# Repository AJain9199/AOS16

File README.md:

<!-- Improved compatibility of back to top link: See: https://github.com/othneildrew/Best-README-Template/pull/73 -->

<!--
*** Thanks for checking out the Best-README-Template. If you have a suggestion
*** that would make this better, please fork the repo and create a pull request
*** or simply open an issue with the tag "enhancement".
*** Don't forget to give the project a star!
*** Thanks again! Now go create something AMAZING! :D
-->

<!-- PROJECT SHIELDS -->
<!--
*** I'm using markdown "reference style" links for readability.
*** Reference links are enclosed in brackets [ ] instead of parentheses ( ).
*** See the bottom of this document for the declaration of the reference variables
*** for contributors-url, forks-url, etc. This is an optional, concise syntax you may use.
*** https://www.markdownguide.org/basic-syntax/#reference-style-links
-->

<!-- PROJECT LOGO -->
<br />
<div align="center">
    
    <h1 align="center">AOS16</h1>
  <p align="center">
    A self-made 16-bit computer.
  </p>
</div>

<!-- TABLE OF CONTENTS -->
<details>
  <summary>Table of Contents</summary>
  <ol>
    <li>
      <a href="#about-the-project">About The Project</a>
    </li>
    <li><a href="#pictures">Pictures</a></li>
    <li><a href="#technical-details">Technical Details</a></li>
    <li><a href="#directory-structure">Directory Structure</a></li>
    <li><a href="#to-do">To-Do</a></li>
    <li><a href="#acknowledgments">Acknowledgments</a></li>
  </ol>
</details>

<!-- ABOUT THE PROJECT -->

## About The Project

AOS16 is a self-made 16-bit Reduced Instruction Set Computer (RISC) on PCBs, complete with a homebrew GPU for screen output. It is fully planned, designed and fabricated from scratch. A Turing-complete, Harvard-style computer with a completely custom architecture, at a blistering fast 10MHz.

The project is divided into smaller subsytems on PCBs, designed to interconnect via a central bus.

### Features
- 16-bit address and data buses
- Hardware double buffering with parallel CPU and GPU operation
- 10 MHz clock
- 6 general-purpose registers, a stack pointer and a flags register
- 65 Kb of general purpose RAM
- 131 Kb of framebuffer (double buffered, so 65Kb usable)
- 131 Kb of program memory

### Why?

This project was a learning effort for me. I started this project wanting to learn more about computer architectures and gain hands-on experience with electrical engineering. Also, building a computer, from scratch, is the coolest project I've seen around. Some inspiration from amazing engineers including Ben Eater and jdh were more than enough to convince me to try my hand at this project.

### How's it different?

Most homebrew computers on the internet are 8-bit computers built on breadboards.  AOS16 is novel in its capabilities, being a 16-bit computer built on PCBs with a much higher clock speed, with display support directly integrated. 

<p align="right">(<a href="#readme-top">back to top</a>)</p>

## Pictures

<!-- The animated GIFs will not be visible in the PDF! Please visit the repository on [Github](https://github.com/AJain9199/AOS16). -->

<h2 align="center">
A simulation of the computer in Digital displaying the color palette on the screen
</h2>

<br>

<h2 align="center">
    GPU displaying the pillars of creation
</h2>

<br>

<h2 align="center">
    The Arithmetic Logic Unit in KiCAD
</h2>

<br>

<h2 align="center">
    The logic simulation in Digital.
</h2>

<br>

<h2 align="center">
    The Reg4x16 PCB 
</h2>

<br>

.jpeg>)

<h2 align="center">
    The Double Buffer PCB
</h2>

<br>

<p align="right">(<a href="#readme-top">back to top</a>)</p>

## Technical Details

Details about the design decisions, design of the instruction word, etc. can be found in the [Design Doc](AOS-16%20Design.md).

## Directory Structure

- assembler: Contains the source code for the AOS16 assembler
- sim: Logic simulation files written for Digital
- microcode: Microcode implementations written in MiLa
- tests: some basic tests for ICs and the simulation
- common: basic KiCAD schematics (registers, transceivers) which are shared across subsystems

Each of the remaining folders represents a subsystem, built on a separate PCB. Each folder will contain a KiCAD schematic and PCB file.

## To-do

Main Phases of the project:

-   [x] Finalize project parameters and design goals
-   [ ] Hardware:
    -   [x] Logic Simulation and Design
    -   [ ] PCB Design
    -   [ ] PCB Fabrication & integration
-   [x] Software:
    -   [x] Microcode (with [MiLa](https://github.com/AJain9199/MiLa))
    -   [x] Assembly language design
    -   [x] Assembler
    -   [x] ROM programming software

<br>

| Component / Phase   | Logic Simulation | PCB Design | Fabrication and Integration |
| ------------------- | ---------------- | ---------- | --------------------------- |
| Double Buffer       | ✅               | ✅         | ✅                 |
| Memory Controller   | ✅               | ✅         | ✅                 |
| ALU                 | ✅               | ✅         | ✅                          |
| Registers           | ✅               | ✅         | ✅                          |
| Control Unit        | ✅               | ✅          |  ✅                          |
| Program Counter     | ✅               | ✅         |  ☐                           |
| GPU                 | ✅               | ✅          | ☐                           |
| Main Data Bus       | ✅               | ✅          | ☐                           |
| **Phase Completed** | ✅               | ✅          | ☐                           |

<p align="right">(<a href="#readme-top">back to top</a>)</p>

<!-- ACKNOWLEDGMENTS -->
## Acknowledgments

-   [Ben Eater](https://www.youtube.com/@BenEater) for his excellent series on the breadboard computer
-   [jdh](https://www.youtube.com/@jdh) for the inspiration
-   The Elements of Computing Systems and the accompanying [Nand2Tetris](https://www.nand2tetris.org/) course by Shimon Schocken and Noam Nisan
-   [r/homebrewcomputer](https://www.reddit.com/r/homebrewcomputer/) and [r/PrintedCircuitBoard](https://www.reddit.com/r/PrintedCircuitBoard/) commmunities for PCB reviews and design checks
-   [Digital](https://github.com/hneemann/Digital), the logic simulator

<p align="right">(<a href="#readme-top">back to top</a>)</p>

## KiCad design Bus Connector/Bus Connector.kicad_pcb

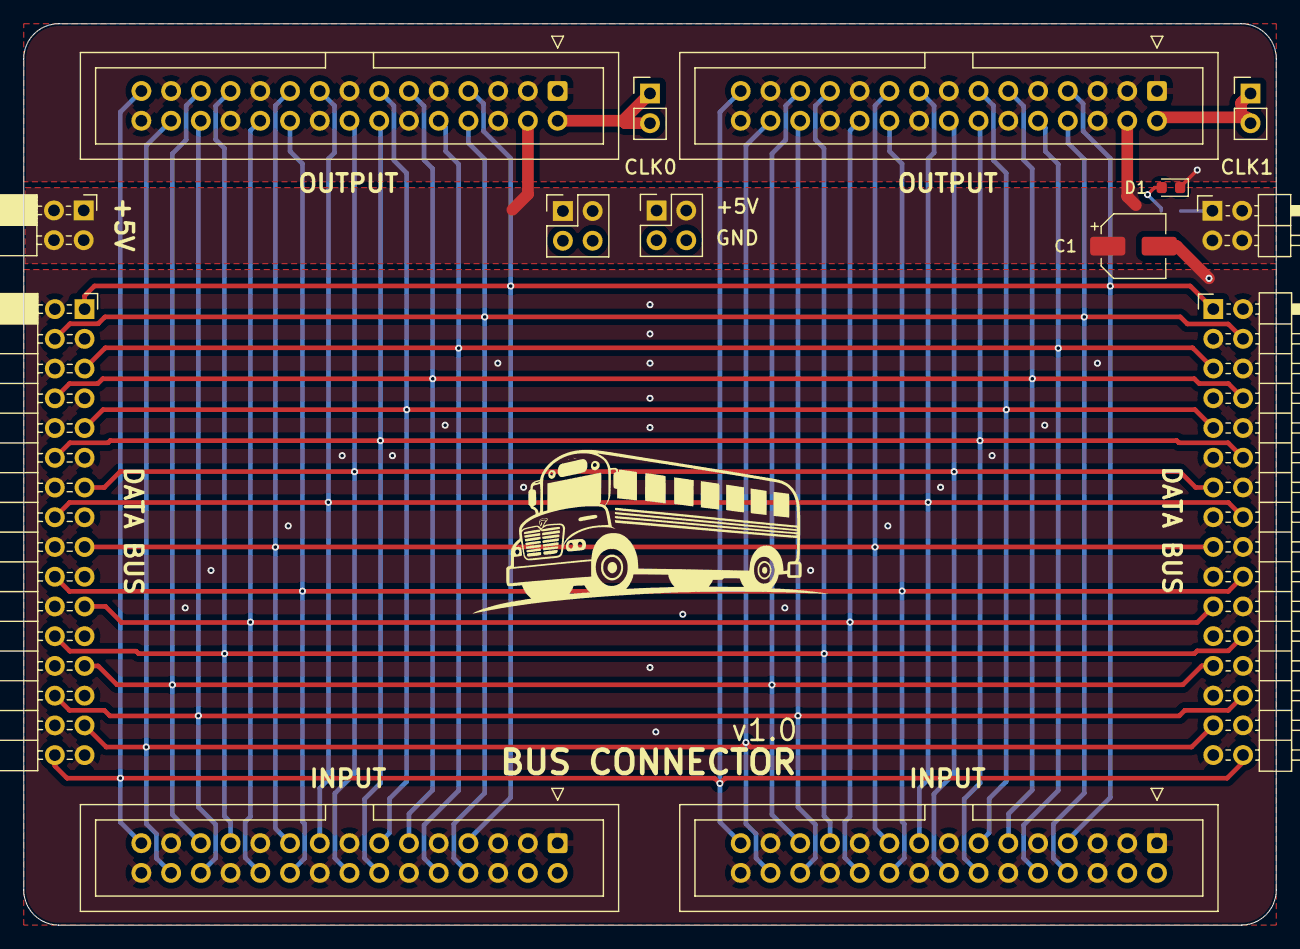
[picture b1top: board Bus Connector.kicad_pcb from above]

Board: 2 copper layers, 107.0 x 77.0 mm, 15 parts (1 on the bottom side), 21 nets.

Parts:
C1: 100uF; CP_Elec_5x5.3
D1: LED; LED_0603_1608Metric
J1: Conn_02x16_Odd_Even; PinSocket_2x16_P2.54mm_Horizontal
J2: Conn_02x16_Odd_Even; PinHeader_2x16_P2.54mm_Horizontal
J3: Conn_02x02_Counter_Clockwise; PinHeader_2x02_P2.54mm_Horizontal
J4: Conn_02x02_Counter_Clockwise; PinSocket_2x02_P2.54mm_Horizontal
J5, J6, J7, J8: Conn_02x15_Odd_Even; IDC-Header_2x15_P2.54mm_Vertical
J9, J10: Conn_01x02_Pin; PinHeader_1x02_P2.54mm_Vertical
J11, J12: Conn_02x02_Counter_Clockwise; PinHeader_2x02_P2.54mm_Vertical
R1: 220; R_0603_1608Metric

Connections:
+5V: C1.1, J3.1, J3.2, J3.3, J3.4, J4.1, J4.2, J4.3, J4.4, J7.4, J8.4, J11.1, J11.2, J12.1, J12.2, R1.1
/IO0: J1.1, J2.1, J5.7, J6.7, J7.7, J8.7
/IO1: J1.4, J2.4, J5.8, J6.8, J7.8, J8.8
/IO2: J1.5, J2.5, J5.10, J6.10, J7.10, J8.10
/IO3: J1.8, J2.8, J5.11, J6.11, J7.11, J8.11
/IO4: J1.9, J2.9, J5.13, J6.13, J7.13, J8.13
/IO5: J1.12, J2.12, J5.14, J6.14, J7.14, J8.14
/IO6: J1.13, J2.13, J5.16, J6.16, J7.16, J8.16
/IO7: J1.16, J2.16, J5.17, J6.17, J7.17, J8.17
/IO8: J1.17, J2.17, J5.19, J6.19, J7.19, J8.19
/IO9: J1.20, J2.20, J5.20, J6.20, J7.20, J8.20
/IO10: J1.21, J2.21, J5.22, J6.22, J7.22, J8.22
/IO11: J1.24, J2.24, J5.23, J6.23, J7.23, J8.23
/IO12: J1.25, J2.25, J5.25, J6.25, J7.25, J8.25
/IO13: J1.28, J2.28, J5.26, J6.26, J7.26, J8.26
/IO14: J1.29, J2.29, J5.28, J6.28, J7.28, J8.28
/IO15: J1.32, J2.32, J5.29, J6.29, J7.29, J8.29
/bus_conn2/CLK: J7.2, J10.1, J10.2
/bus_conn3/CLK: J8.2, J9.1, J9.2
GND: C1.2, D1.1 (K), J1.2, J1.3, J1.6, J1.7, J1.10, J1.11, J1.14, J1.15, J1.18, J1.19, J1.22, J1.23, J1.26, J1.27, J1.30, J1.31, J2.2, J2.3, J2.6, J2.7, J2.10, J2.11, J2.14, J2.15, J2.18, J2.19, J2.22, J2.23, J2.26, J2.27, J2.30, J2.31, J5.1, J5.3, J5.5, J5.6, J5.9, J5.12, J5.15, J5.18, J5.21, J5.24, J5.27, J5.30, J6.1, J6.3, J6.5, J6.6, J6.9, J6.12, J6.15, J6.18, J6.21, J6.24, J6.27, J6.30, J7.1, J7.3, J7.5, J7.6, J7.9, J7.12, J7.15, J7.18, J7.21, J7.24, J7.27, J7.30, J8.1, J8.3, J8.5, J8.6, J8.9, J8.12, J8.15, J8.18, J8.21, J8.24, J8.27, J8.30, J11.3, J11.4, J12.3, J12.4
unnamed: D1.2 (A), R1.2

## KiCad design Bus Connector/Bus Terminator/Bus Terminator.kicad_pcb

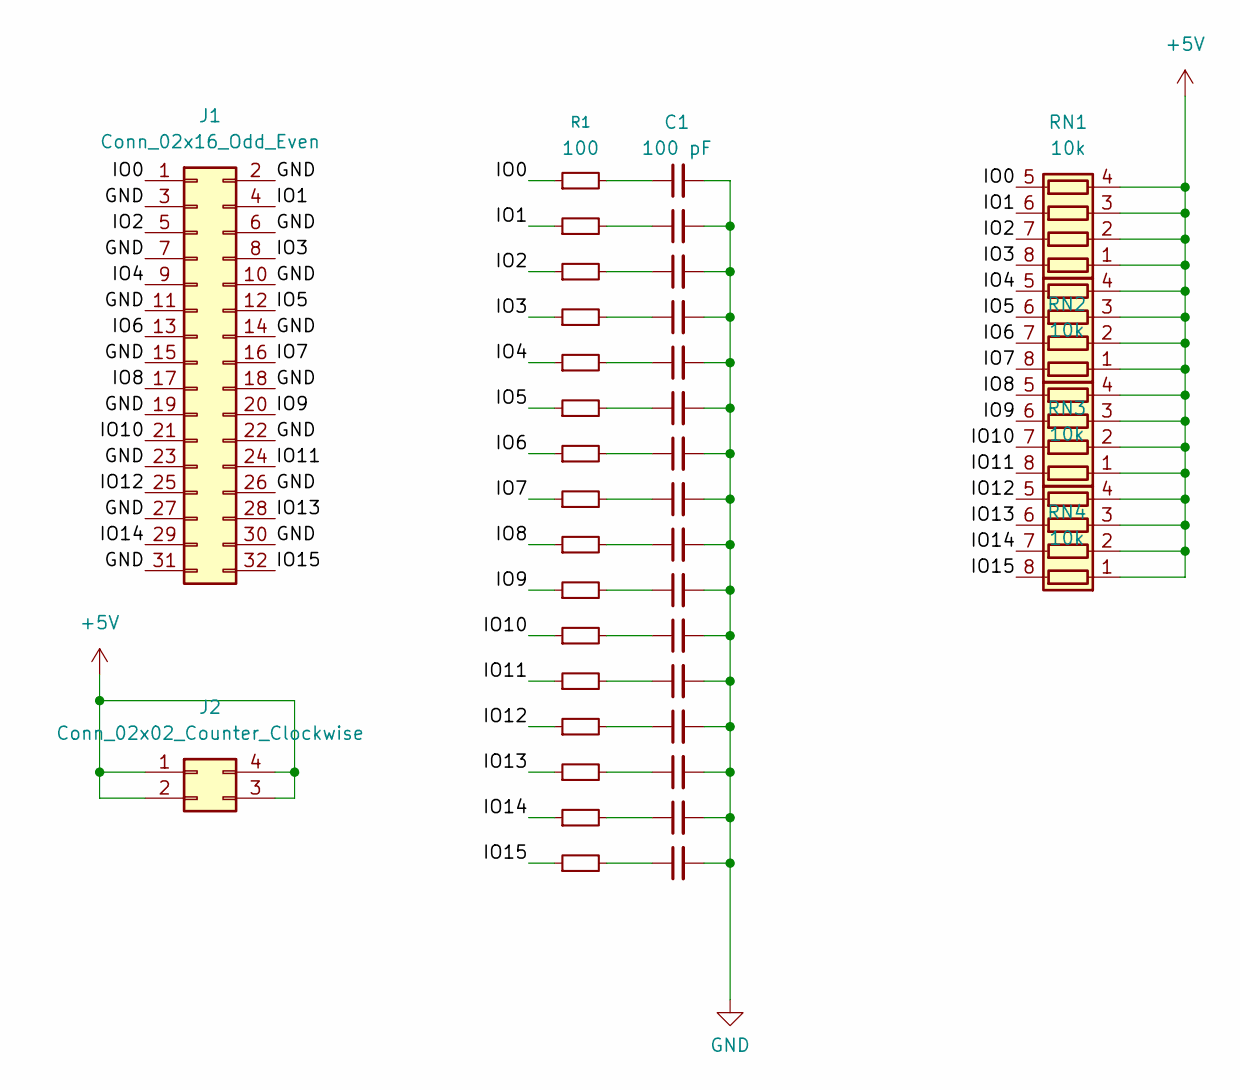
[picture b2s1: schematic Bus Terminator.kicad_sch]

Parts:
C1, C2, C3, C4, C5, C6, C7, C8, C9, C10, C11, C12, C13, C14, C15, C16: 100 pF; C_0603_1608Metric
J1: Conn_02x16_Odd_Even; PinHeader_2x16_P2.54mm_Horizontal
J2: Conn_02x02_Counter_Clockwise; PinHeader_2x02_P2.54mm_Horizontal
R1, R2, R3, R4, R5, R6, R7, R8, R9, R10, R11, R12, R13, R14, R15, R16: 100; R_0603_1608Metric
RN1, RN2, RN3, RN4: 10k; R_Array_Convex_4x1206

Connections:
+5V: J2.1, J2.2, J2.3, J2.4, RN1.1 (R1.1), RN1.2 (R2.1), RN1.3 (R3.1), RN1.4 (R4.1), RN2.1 (R1.1), RN2.2 (R2.1), RN2.3 (R3.1), RN2.4 (R4.1), RN3.1 (R1.1), RN3.2 (R2.1), RN3.3 (R3.1), RN3.4 (R4.1), RN4.1 (R1.1), RN4.2 (R2.1), RN4.3 (R3.1), RN4.4 (R4.1)
/IO0: J1.1, R1.1, RN1.5 (R4.2)
/IO1: J1.4, R2.1, RN1.6 (R3.2)
/IO2: J1.5, R3.1, RN1.7 (R2.2)
/IO3: J1.8, R4.1, RN1.8 (R1.2)
/IO4: J1.9, R5.1, RN2.5 (R4.2)
/IO5: J1.12, R6.1, RN2.6 (R3.2)
/IO6: J1.13, R7.1, RN2.7 (R2.2)
/IO7: J1.16, R8.1, RN2.8 (R1.2)
/IO8: J1.17, R9.1, RN3.5 (R4.2)
/IO9: J1.20, R10.1, RN3.6 (R3.2)
/IO10: J1.21, R11.1, RN3.7 (R2.2)
/IO11: J1.24, R12.1, RN3.8 (R1.2)
/IO12: J1.25, R13.1, RN4.5 (R4.2)
/IO13: J1.28, R14.1, RN4.6 (R3.2)
/IO14: J1.29, R15.1, RN4.7 (R2.2)
/IO15: J1.32, R16.1, RN4.8 (R1.2)
GND: C1.2, C2.2, C3.2, C4.2, C5.2, C6.2, C7.2, C8.2, C9.2, C10.2, C11.2, C12.2, C13.2, C14.2, C15.2, C16.2, J1.2, J1.3, J1.6, J1.7, J1.10, J1.11, J1.14, J1.15, J1.18, J1.19, J1.22, J1.23, J1.26, J1.27, J1.30, J1.31
unnamed: C1.1, R1.2
unnamed: C2.1, R2.2
unnamed: C3.1, R3.2
unnamed: C4.1, R4.2
unnamed: C5.1, R5.2
unnamed: C6.1, R6.2
unnamed: C7.1, R7.2
unnamed: C8.1, R8.2
unnamed: C9.1, R9.2
unnamed: C10.1, R10.2
unnamed: C11.1, R11.2
unnamed: C12.1, R12.2
unnamed: C13.1, R13.2
unnamed: C14.1, R14.2
unnamed: C15.1, R15.2
unnamed: C16.1, R16.2

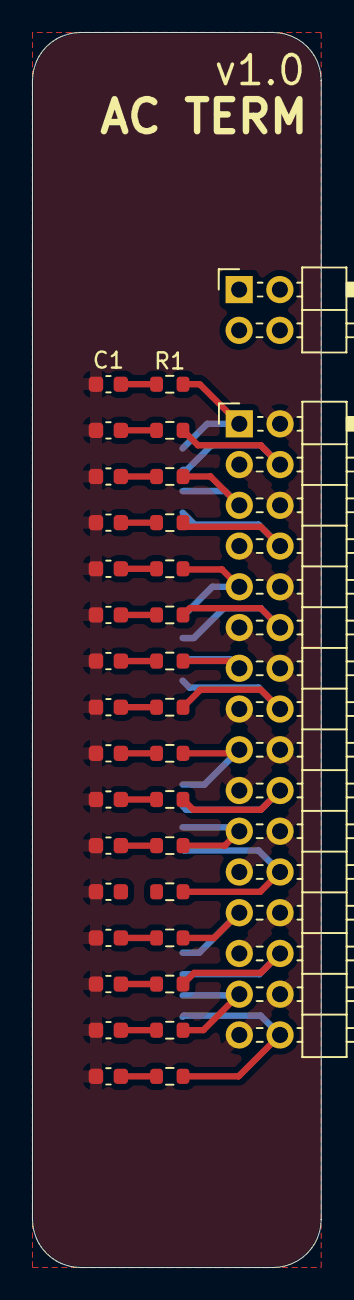
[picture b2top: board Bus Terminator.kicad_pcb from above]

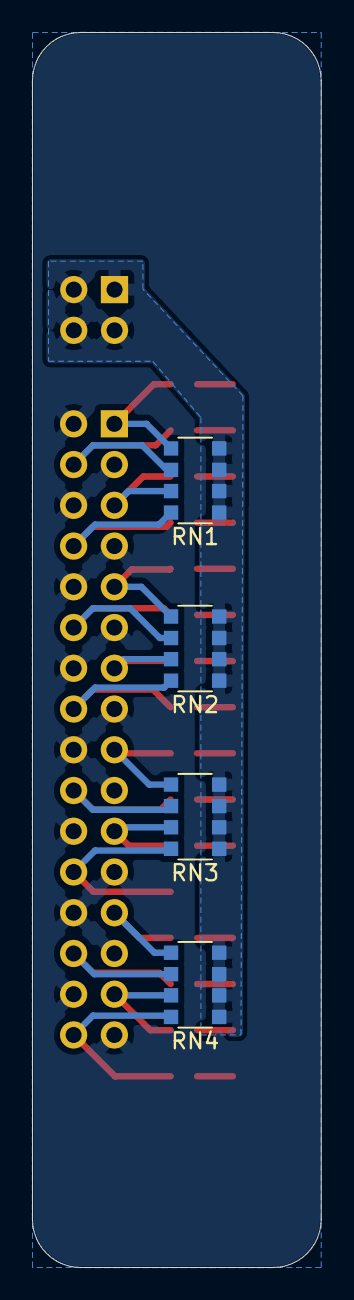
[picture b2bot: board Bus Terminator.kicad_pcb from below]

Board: 2 copper layers, 18.0 x 77.0 mm, 38 parts (4 on the bottom side), 34 nets.

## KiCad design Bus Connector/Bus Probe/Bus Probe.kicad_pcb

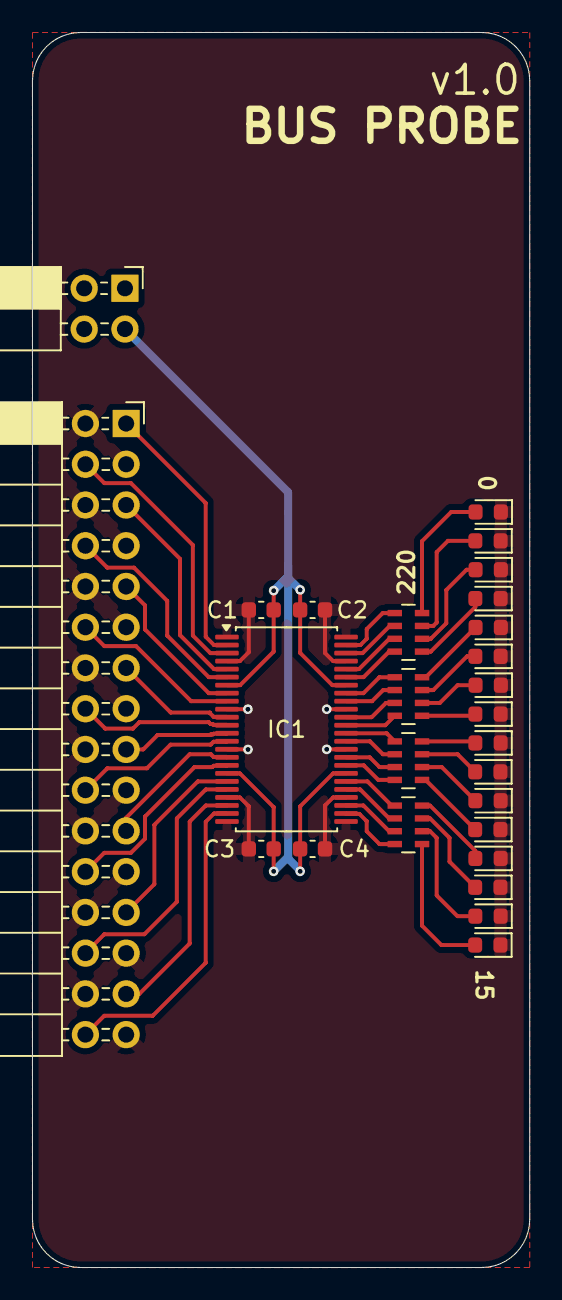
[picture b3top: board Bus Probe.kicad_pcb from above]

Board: 2 copper layers, 31.0 x 77.0 mm, 27 parts (0 on the bottom side), 50 nets.

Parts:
C1, C2, C3, C4: 0.01uF; C_0603_1608Metric
D1, D2, D3, D4, D5, D6, D7, D8, D9, D10, D11, D12, D13, D14, D15, D16: LED_Small; LED_0603_1608Metric
IC1: SN74AHCT16245DGGR; TSSOP-48_6.1x12.5mm_P0.5mm
J1: Conn_02x16_Odd_Even; PinSocket_2x16_P2.54mm_Horizontal
J2: Conn_02x02_Counter_Clockwise; PinSocket_2x02_P2.54mm_Horizontal
RN1, RN2, RN3, RN4: R_Pack04; R_Array_Concave_4x0603

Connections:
+5V: C1.1, C2.1, C3.1, C4.1, IC1.7 (VCC), IC1.18 (VCC), IC1.31 (VCC), IC1.42 (VCC), J2.1, J2.2, J2.3, J2.4
/B0: IC1.47 (A0), RN1.1 (R1.1)
/B1: IC1.46 (A1), RN1.2 (R2.1)
/B2: IC1.44 (A2), RN1.3 (R3.1)
/B3: IC1.43 (A3), RN1.4 (R4.1)
/B4: IC1.41 (A4), RN2.1 (R1.1)
/B5: IC1.40 (A5), RN2.2 (R2.1)
/B6: IC1.38 (A6), RN2.3 (R3.1)
/B7: IC1.37 (A7), RN2.4 (R4.1)
/B8: IC1.36 (A8), RN3.1 (R1.1)
/B9: IC1.35 (A9), RN3.2 (R2.1)
/B10: IC1.33 (A10), RN3.3 (R3.1)
/B11: IC1.32 (A11), RN3.4 (R4.1)
/B12: IC1.30 (A12), RN4.1 (R1.1)
/B13: IC1.29 (A13), RN4.2 (R2.1)
/B14: IC1.27 (A14), RN4.3 (R3.1)
/B15: IC1.26 (A15), RN4.4 (R4.1)
/IO0: IC1.2 (B0), J1.1
/IO1: IC1.3 (B1), J1.4
/IO2: IC1.5 (B2), J1.5
/IO3: IC1.6 (B3), J1.8
/IO4: IC1.8 (B4), J1.9
/IO5: IC1.9 (B5), J1.12
/IO6: IC1.11 (B6), J1.13
/IO7: IC1.12 (B7), J1.16
/IO8: IC1.13 (B8), J1.17
/IO9: IC1.14 (B9), J1.20
/IO10: IC1.16 (B10), J1.21
/IO11: IC1.17 (B11), J1.24
/IO12: IC1.19 (B12), J1.25
/IO13: IC1.20 (B13), J1.28
/IO14: IC1.22 (B14), J1.29
/IO15: IC1.23 (B15), J1.32
GND: C1.2, C2.2, C3.2, C4.2, D1.1 (K), D2.1 (K), D3.1 (K), D4.1 (K), D5.1 (K), D6.1 (K), D7.1 (K), D8.1 (K), D9.1 (K), D10.1 (K), D11.1 (K), D12.1 (K), D13.1 (K), D14.1 (K), D15.1 (K), D16.1 (K), IC1.1 (T/~R1), IC1.4 (GND), IC1.10 (GND), IC1.15 (GND), IC1.21 (GND), IC1.24 (T/~R2), IC1.25 (~OE2), IC1.28 (GND), IC1.34 (GND), IC1.39 (GND), IC1.45 (GND), IC1.48 (~OE1), J1.2, J1.3, J1.6, J1.7, J1.10, J1.11, J1.14, J1.15, J1.18, J1.19, J1.22, J1.23, J1.26, J1.27, J1.30, J1.31
unnamed: D1.2 (A), RN1.8 (R1.2)
unnamed: D2.2 (A), RN1.6 (R3.2)
unnamed: D3.2 (A), RN2.8 (R1.2)
unnamed: D4.2 (A), RN2.6 (R3.2)
unnamed: D5.2 (A), RN3.8 (R1.2)
unnamed: D6.2 (A), RN3.6 (R3.2)
unnamed: D7.2 (A), RN4.8 (R1.2)
unnamed: D8.2 (A), RN4.6 (R3.2)
unnamed: D9.2 (A), RN1.7 (R2.2)
unnamed: D10.2 (A), RN1.5 (R4.2)
unnamed: D11.2 (A), RN2.7 (R2.2)
unnamed: D12.2 (A), RN2.5 (R4.2)
unnamed: D13.2 (A), RN3.7 (R2.2)
unnamed: D14.2 (A), RN3.5 (R4.2)
unnamed: D15.2 (A), RN4.7 (R2.2)
unnamed: D16.2 (A), RN4.5 (R4.2)

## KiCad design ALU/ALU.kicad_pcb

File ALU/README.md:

# Arithmetic Logic Unit
The Arithmetic Logic Unit is one of the the first PCBs I designed and built as part of the project. It is essentially a wrapper for the 74LS181 ICs, 4 of them handling each of the 4 nibbles, with additional circuitry to manage the IO and carry generation for each of the 4 chips.

```mermaid
flowchart LR
	porta@{ shape: lean-r, label: "PORT A"}
	latcha["`Latch A`"]
	porta --> latcha
	ina((INA))
	ina --> latcha
	
	portb@{ shape: lean-r, label: "PORT B"}
	latchb["`Latch B`"]
	portb --> latchb
	inb((INB))
	inb --> latchb
	
	subgraph alu [Arithmetic Unit]
		aluchip1@{ shape: subproc, label: "74LS181 A" }
		aluchip2@{ shape: subproc, label: "74LS181 B" }
		aluchip3@{ shape: subproc, label: "74LS181 C" }
		aluchip4@{ shape: subproc, label: "74LS181 D" }
		
		carrygen["`Carry Generator`"]
		
		carrygen --> aluchip1
		carrygen --> aluchip2
		carrygen --> aluchip3
		carrygen --> aluchip4
	end
	
	latcha --> alu
	latchb --> alu
	
	buffer@{shape: tri, label: "Tri-State Buffer"}
	noe((nOE))
	noe --> buffer
	
	alu --> buffer --> outport
	carryout((nCo))
	alu --> carryout
	
	alus(["`S[0..3]`"]) --> alu
	m((M)) --> alu
	cin((nCin)) --> alu
	
	outport@{ shape: lean-r, label: "OUTPUT"}
```

## Carry Generation

Since each 74LS181 chip only handles 4 bits, 4 of these chips need to be used together. Instead of cascading them using the built-in carry outputs, I used full look-ahead carry generation which is more than 2x faster ([sn54s181](../datasheets/sn54s181.pdf)) (realistically both are fine at the speeds this works at, this is simply future/idiot proofing) But I couldn't find the carry generation chip, the 182, so I replicated the internal circuit using discrete (A)HCT gates ([sn54s182](../datasheets/sn54s182.pdf)).

Since I wasn't sure if this will work, I added test pads on the cascade carry outputs and inputs so they could be used as a contingency.

## Latches
The 181s need both A and B inputs driven at the same time to function correctly. Since they ultimately need to be driven by the same bus, the inputs are latched using separate signals which drive the physical inputs. I considered adding a second bus only to drive port B, but the added complexity was not worth the benefit of saving 1-2 microcode instructions and 2 control signals.

Inputs are latched at the rising edge. The AHCT16374's ([sn74ahct16374](../datasheets/sn74ahct16374.pdf)) are asynchronous, so the latching input is and'ed with the clock to make them "synchronous."

## Iterations
- v1.0: The control signals on the 16374 were routed wrong due to a schematic symbol mismatch
- v1.1: The 16374 was routed wrong (again)
- v1.2: Final

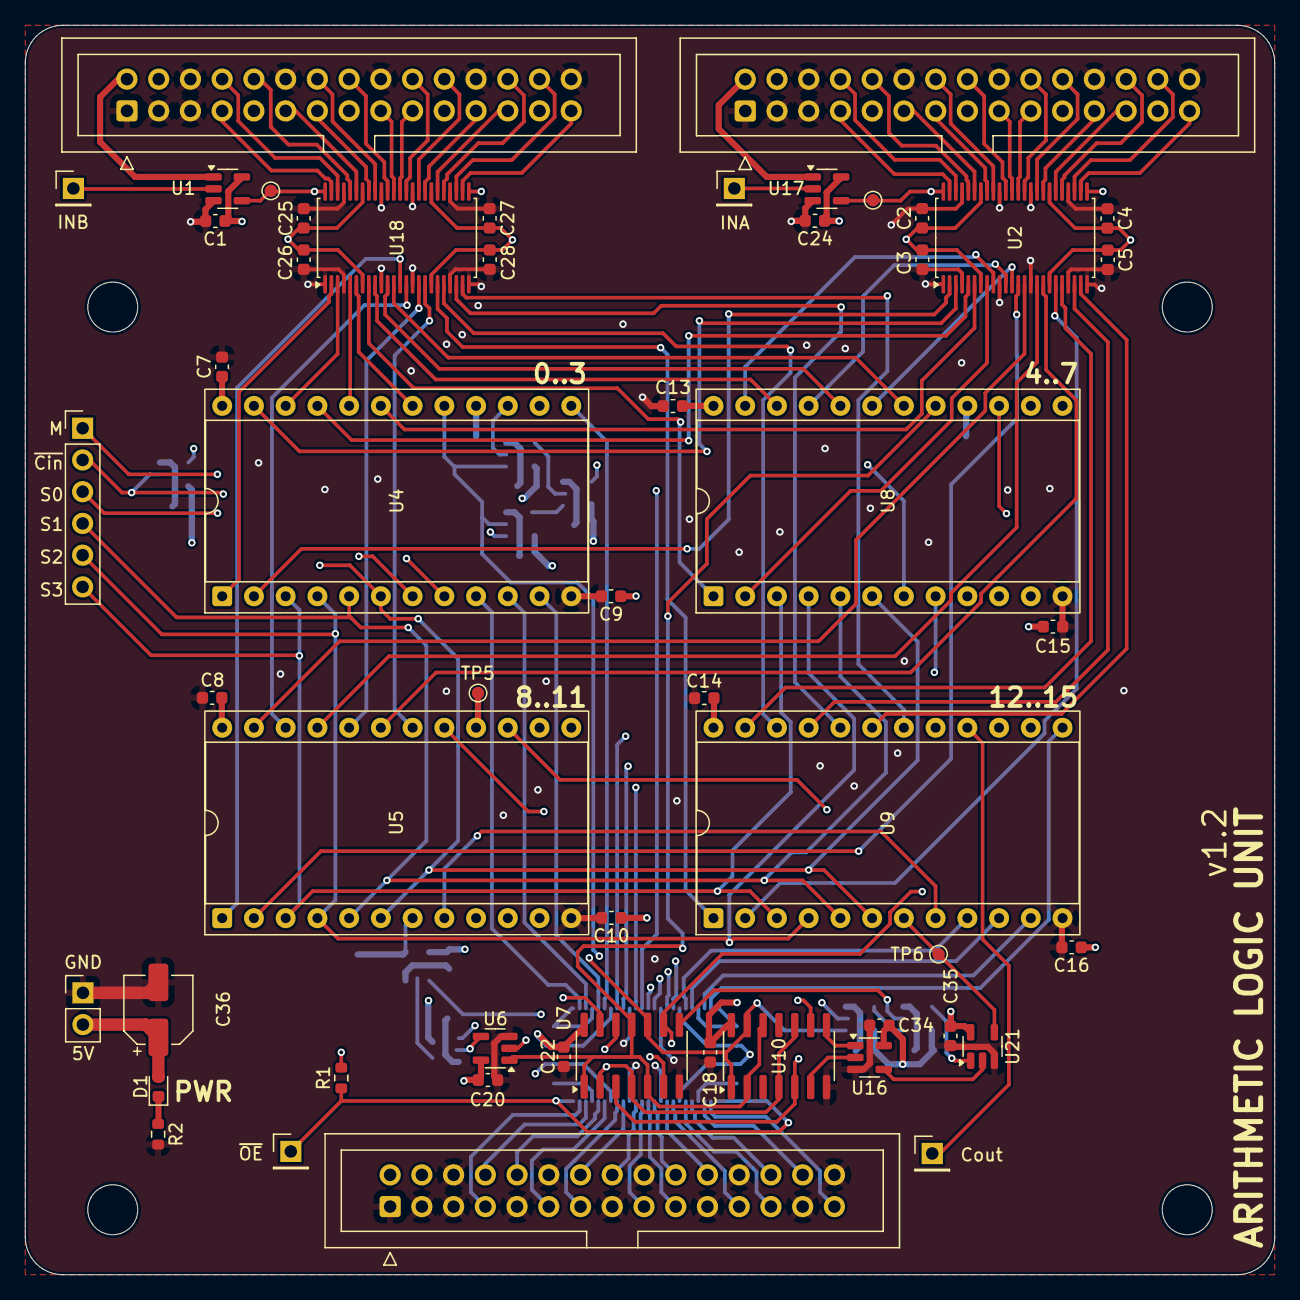
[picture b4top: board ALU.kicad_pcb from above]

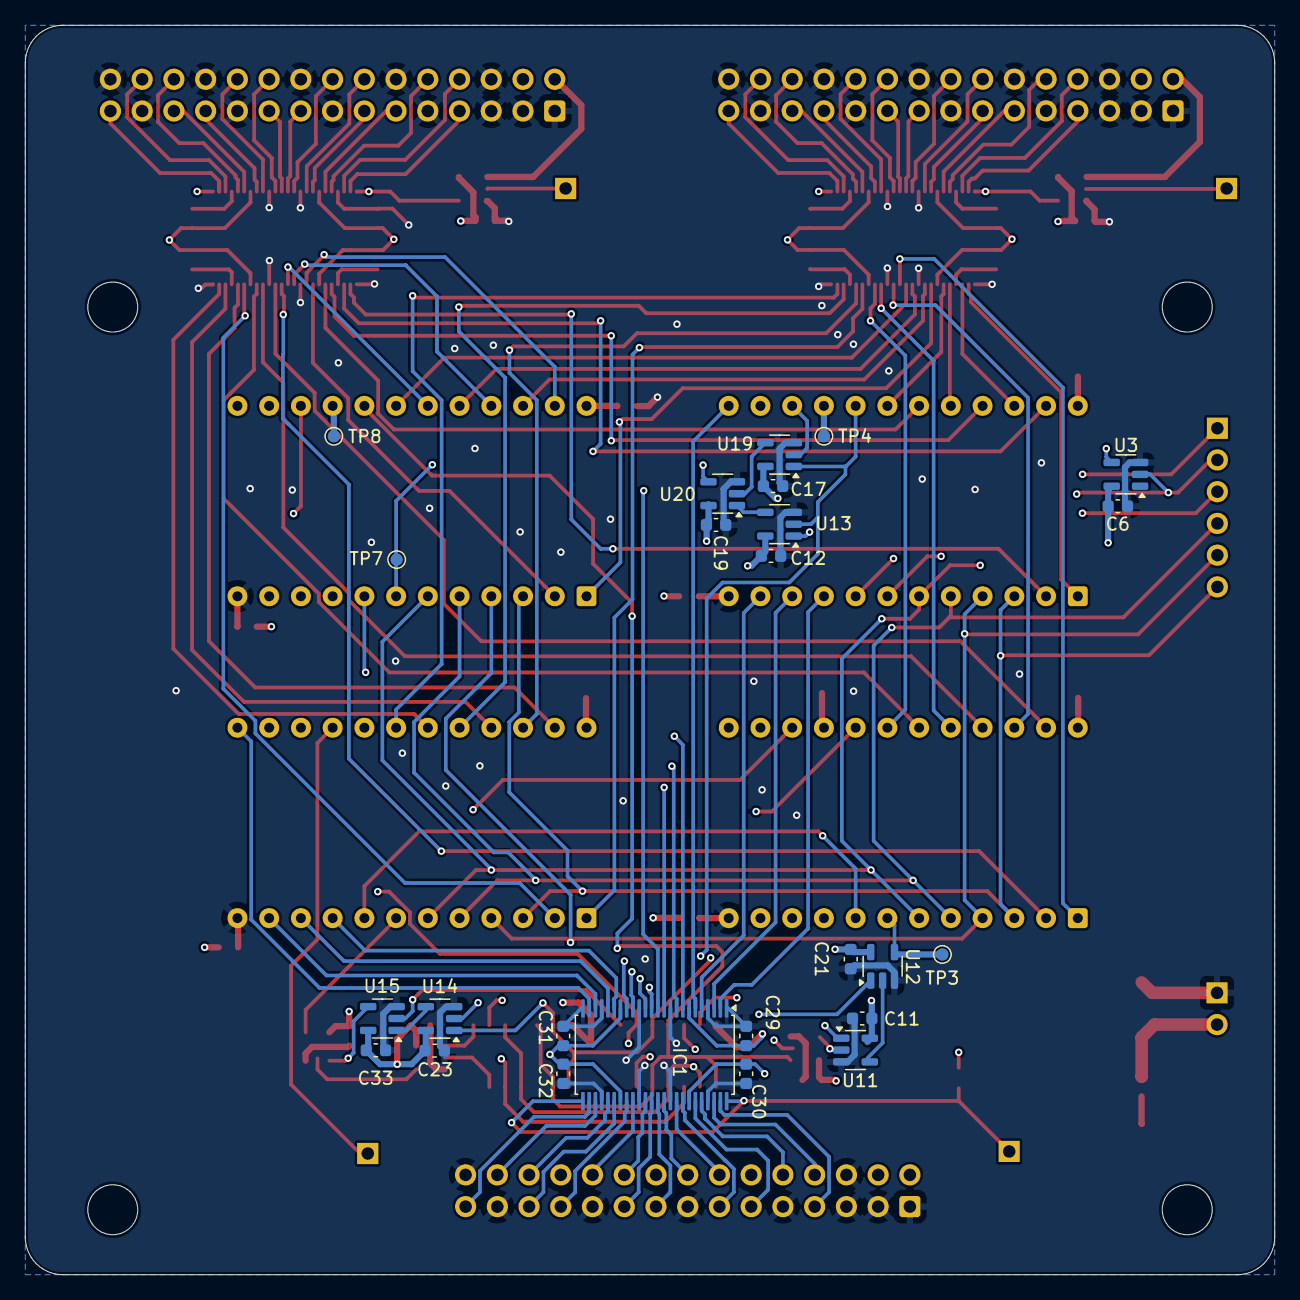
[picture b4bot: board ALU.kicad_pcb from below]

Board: 4 copper layers, 100.0 x 100.0 mm, 82 parts (25 on the bottom side), 138 nets.

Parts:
C1, C6, C7, C8, C9, C10, C11, C12, C13, C14, C15, C16, C17, C18, C19, C20, C21, C22, C23, C24, C33, C34, C35: 0.1uF; C_0603_1608Metric
C2, C3, C4, C5, C25, C26, C27, C28, C29, C30, C31, C32: 0.01uF; C_0603_1608Metric
C36: 100uF; CP_Elec_5x5.3
D1: LED; LED_0603_1608Metric
H1, H2, H3, H4: MountingHole; MountingHole_4mm
IC1: SN74AHCT16245DGGR; TSSOP-48_6.1x12.5mm_P0.5mm
J1: Conn_01x06_Pin; PinHeader_1x06_P2.54mm_Vertical
J2, J3, J4: Conn_02x15_Odd_Even; IDC-Header_2x15_P2.54mm_Vertical
J5, J6, J7, J8: Conn_01x01_Pin; PinHeader_1x01_P2.54mm_Vertical
J9: Conn_01x02; PinHeader_1x02_P2.54mm_Vertical
R1: 1k; R_0603_1608Metric
R2: 100; R_0603_1608Metric
TP1, TP2, TP3, TP4, TP5, TP6, TP7, TP8: TestPoint; TestPoint_Pad_D1.0mm
U1, U17: 74AHC1G08; SOT-23-5
U2, U18: SN74AHCT16374DGGR; TSSOP-48_6.1x12.5mm_P0.5mm
U3: 74AHC1G04DBVR; SOT-23-5
U4, U5, U8, U9: 74LS181; DIP-24_W15.24mm_Socket
U6, U13, U14, U19: 74AHCT1G08DBVR; SOT-23-5
U7: 74HCT11; SOIC-14_3.9x8.7mm_P1.27mm
U10: 74HCT21; SOIC-14_3.9x8.7mm_P1.27mm
U11, U15, U16: 74AHC1G32DBVR; SOT-23-5
U12, U20, U21: 74AHCT1G02DBVR; SOT-23-5

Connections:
+5V: C1.1, C2.1, C3.1, C4.1, C5.1, C6.1, C7.1, C8.1, C9.1, C10.1, C11.1, C12.1, C13.1, C14.1, C15.1, C16.1, C17.1, C18.1, C19.1, C20.1, C21.1, C22.1, C23.1, C24.1, C25.1, C26.1, C27.1, C28.1, C29.1, C30.1, C31.1, C32.1, C33.1, C34.1, C35.1, C36.1, D1.2 (A), IC1.7 (VCC), IC1.18 (VCC), IC1.31 (VCC), IC1.42 (VCC), J2.4, J3.4, J9.2, R1.2, U1.5 (VCC), U2.7 (VCC_1), U2.18 (VCC_2), U2.31 (VCC), U2.42 (VCC_4), U3.5 (VCC), U4.24 (VCC), U5.24 (VCC), U6.5 (VCC), U7.14 (VCC), U8.24 (VCC), U9.24 (VCC), U10.14 (VCC), U11.5 (VCC), U12.5 (VCC), U13.5 (VCC), U14.5 (VCC), U15.5 (VCC), U16.5 (VCC), U17.5 (VCC), U18.7 (VCC_1), U18.18 (VCC_2), U18.31 (VCC), U18.42 (VCC_4), U19.5 (VCC), U20.5 (VCC), U21.5 (VCC)
/INA: J5.1, U17.2
/INA/DIN0: J2.7, U2.47 (1D1)
/INA/DIN1: J2.8, U2.46 (1D2)
/INA/DIN2: J2.10, U2.44 (1D3)
/INA/DIN3: J2.11, U2.43 (1D4)
/INA/DIN4: J2.13, U2.41 (1D5)
/INA/DIN5: J2.14, U2.40 (1D6)
/INA/DIN6: J2.16, U2.38 (1D7)
/INA/DIN7: J2.17, U2.37 (1D8)
/INA/DIN8: J2.19, U2.36 (2D1)
/INA/DIN9: J2.20, U2.35 (2D2)
/INA/DIN10: J2.22, U2.33 (2D3)
/INA/DIN11: J2.23, U2.32 (2D4)
/INA/DIN12: J2.25, U2.30 (2D5)
/INA/DIN13: J2.26, U2.29 (2D6)
/INA/DIN14: J2.28, U2.27 (2D7)
/INA/DIN15: J2.29, U2.26 (2D8)
/INA/DOUT0: U2.2 (1Q1), U4.2 (A0)
/INA/DOUT1: U2.3 (1Q2), U4.23 (A1)
/INA/DOUT2: U2.5 (1Q3), U4.21 (A2)
/INA/DOUT3: U2.6 (1Q4), U4.19 (A3)
/INA/DOUT4: U2.8 (1Q5), U8.2 (A0)
/INA/DOUT5: U2.9 (1Q6), U8.23 (A1)
/INA/DOUT6: U2.11 (1Q7), U8.21 (A2)
/INA/DOUT7: U2.12 (1Q8), U8.19 (A3)
/INA/DOUT8: U2.13 (2Q1), U5.2 (A0)
/INA/DOUT9: U2.14 (2Q2), U5.23 (A1)
/INA/DOUT10: U2.16 (2Q3), U5.21 (A2)
/INA/DOUT11: U2.17 (2Q4), U5.19 (A3)
/INA/DOUT12: U2.19 (2Q5), U9.2 (A0)
/INA/DOUT13: U2.20 (2Q6), U9.23 (A1)
/INA/DOUT14: U2.22 (2Q7), U9.21 (A2)
/INA/DOUT15: U2.23 (2Q8), U9.19 (A3)
/INB: J6.1, U1.2
/INB/DIN0: J3.7, U18.47 (1D1)
/INB/DIN1: J3.8, U18.46 (1D2)
/INB/DIN2: J3.10, U18.44 (1D3)
/INB/DIN3: J3.11, U18.43 (1D4)
/INB/DIN4: J3.13, U18.41 (1D5)
/INB/DIN5: J3.14, U18.40 (1D6)
/INB/DIN6: J3.16, U18.38 (1D7)
/INB/DIN7: J3.17, U18.37 (1D8)
/INB/DIN8: J3.19, U18.36 (2D1)
/INB/DIN9: J3.20, U18.35 (2D2)
/INB/DIN10: J3.22, U18.33 (2D3)
/INB/DIN11: J3.23, U18.32 (2D4)
/INB/DIN12: J3.25, U18.30 (2D5)
/INB/DIN13: J3.26, U18.29 (2D6)
/INB/DIN14: J3.28, U18.27 (2D7)
/INB/DIN15: J3.29, U18.26 (2D8)
/INB/DOUT0: U4.1 (B0), U18.2 (1Q1)
/INB/DOUT1: U4.22 (B1), U18.3 (1Q2)
/INB/DOUT2: U4.20 (B2), U18.5 (1Q3)
/INB/DOUT3: U4.18 (B3), U18.6 (1Q4)
/INB/DOUT4: U8.1 (B0), U18.8 (1Q5)
/INB/DOUT5: U8.22 (B1), U18.9 (1Q6)
/INB/DOUT6: U8.20 (B2), U18.11 (1Q7)
/INB/DOUT7: U8.18 (B3), U18.12 (1Q8)
/INB/DOUT8: U5.1 (B0), U18.13 (2Q1)
/INB/DOUT9: U5.22 (B1), U18.14 (2Q2)
/INB/DOUT10: U5.20 (B2), U18.16 (2Q3)
/INB/DOUT11: U5.18 (B3), U18.17 (2Q4)
/INB/DOUT12: U9.1 (B0), U18.19 (2Q5)
/INB/DOUT13: U9.22 (B1), U18.20 (2Q6)
/INB/DOUT14: U9.20 (B2), U18.22 (2Q7)
/INB/DOUT15: U9.18 (B3), U18.23 (2Q8)
/M: J1.1, U4.8 (M), U5.8 (M), U8.8 (M), U9.8 (M)
/S0: J1.3, U4.6 (S0), U5.6 (S0), U8.6 (S0), U9.6 (S0)
/S1: J1.4, U4.5 (S1), U5.5 (S1), U8.5 (S1), U9.5 (S1)
/S2: J1.5, U4.4 (S2), U5.4 (S2), U8.4 (S2), U9.4 (S2)
/S3: J1.6, U4.3 (S3), U5.3 (S3), U8.3 (S3), U9.3 (S3)
/Tri-State Buf16/A0: IC1.47 (A0), J4.7
/Tri-State Buf16/A1: IC1.46 (A1), J4.8
/Tri-State Buf16/A2: IC1.44 (A2), J4.10
/Tri-State Buf16/A3: IC1.43 (A3), J4.11
/Tri-State Buf16/A4: IC1.41 (A4), J4.13
/Tri-State Buf16/A5: IC1.40 (A5), J4.14
/Tri-State Buf16/A6: IC1.38 (A6), J4.16
/Tri-State Buf16/A7: IC1.37 (A7), J4.17
/Tri-State Buf16/A8: IC1.36 (A8), J4.19
/Tri-State Buf16/A9: IC1.35 (A9), J4.20
/Tri-State Buf16/A10: IC1.33 (A10), J4.22
/Tri-State Buf16/A11: IC1.32 (A11), J4.23
/Tri-State Buf16/A12: IC1.30 (A12), J4.25
/Tri-State Buf16/A13: IC1.29 (A13), J4.26
/Tri-State Buf16/A14: IC1.27 (A14), J4.28
/Tri-State Buf16/A15: IC1.26 (A15), J4.29
/Tri-State Buf16/B0: IC1.2 (B0), U4.9 (F0)
/Tri-State Buf16/B1: IC1.3 (B1), U4.10 (F1)
/Tri-State Buf16/B2: IC1.5 (B2), U4.11 (F2)
/Tri-State Buf16/B3: IC1.6 (B3), U4.13 (F3)
/Tri-State Buf16/B4: IC1.8 (B4), U8.9 (F0)
/Tri-State Buf16/B5: IC1.9 (B5), U8.10 (F1)
/Tri-State Buf16/B6: IC1.11 (B6), U8.11 (F2)
/Tri-State Buf16/B7: IC1.12 (B7), U8.13 (F3)
/Tri-State Buf16/B8: IC1.13 (B8), U5.9 (F0)
/Tri-State Buf16/B9: IC1.14 (B9), U5.10 (F1)
/Tri-State Buf16/B10: IC1.16 (B10), U5.11 (F2)
/Tri-State Buf16/B11: IC1.17 (B11), U5.13 (F3)
/Tri-State Buf16/B12: IC1.19 (B12), U9.9 (F0)
/Tri-State Buf16/B13: IC1.20 (B13), U9.10 (F1)
/Tri-State Buf16/B14: IC1.22 (B14), U9.11 (F2)
/Tri-State Buf16/B15: IC1.23 (B15), U9.13 (F3)
/Tri-State Buf16/~OE: IC1.25 (~OE2), IC1.48 (~OE1), J7.1, R1.1
/alu16/Cnx: TP7.1, U8.7 (Cn), U20.4
/alu16/Cny: TP3.1, U5.7 (Cn), U12.4
/alu16/Cnz: TP6.1, U9.7 (Cn), U21.4
/alu16/Cout: J8.1, U9.16 (Cn+4)
/alu16/X0: U4.15 (X), U7.3, U10.5, U19.2
/alu16/X1: U6.2, U7.9, U8.15 (X)
/alu16/X2: U5.15 (X), U14.2
/alu16/Y0: U4.17 (Y), U7.2, U7.4, U10.4, U10.10, U13.2, U19.1
/alu16/Y1: U6.1, U7.1, U7.5, U7.11, U8.17 (Y), U10.2, U10.12
/alu16/Y2: U5.17 (Y), U7.10, U10.1, U10.13, U14.1
/alu16/carry generator/Cin: U3.4, U7.13, U10.9, U13.1
/bus_connector2/CLK: J3.2, U1.1
/bus_connector/CLK: J2.2, U17.1
/~Cin: J1.2, U3.2, U4.7 (Cn)
GND: C1.2, C2.2, C3.2, C4.2, C5.2, C6.2, C7.2, C8.2, C9.2, C10.2, C11.2, C12.2, C13.2, C14.2, C15.2, C16.2, C17.2, C18.2, C19.2, C20.2, C21.2, C22.2, C23.2, C24.2, C25.2, C26.2, C27.2, C28.2, C29.2, C30.2, C31.2, C32.2, C33.2, C34.2, C35.2, C36.2, IC1.1 (T/~R1), IC1.4 (GND), IC1.10 (GND), IC1.15 (GND), IC1.21 (GND), IC1.24 (T/~R2), IC1.28 (GND), IC1.34 (GND), IC1.39 (GND), IC1.45 (GND), J2.1, J2.3, J2.5, J2.6, J2.9, J2.12, J2.15, J2.18, J2.21, J2.24, J2.27, J2.30, J3.1, J3.3, J3.5, J3.6, J3.9, J3.12, J3.15, J3.18, J3.21, J3.24, J3.27, J3.30, J4.1, J4.3, J4.5, J4.6, J4.9, J4.12, J4.15, J4.18, J4.21, J4.24, J4.27, J4.30, J9.1, R2.2, U1.3 (GND), U2.1 (1~OE), U2.4 (GND_1), U2.10 (GND_2), U2.15 (GND_3), U2.21 (GND_4), U2.24 (2~OE), U2.28 (GND), U2.34 (GND_6), U2.39 (GND_7), U2.45 (GND_8), U3.3 (GND), U4.12 (GND), U5.12 (GND), U6.3 (GND), U7.7 (GND), U8.12 (GND), U9.12 (GND), U10.7 (GND), U11.3 (GND), U12.3 (GND), U13.3 (GND), U14.3 (GND), U15.3 (GND), U16.3 (GND), U17.3 (GND), U18.1 (1~OE), U18.4 (GND_1), U18.10 (GND_2), U18.15 (GND_3), U18.21 (GND_4), U18.24 (2~OE), U18.28 (GND), U18.34 (GND_6), U18.39 (GND_7), U18.45 (GND_8), U19.3 (GND), U20.3 (GND), U21.3 (GND)
unnamed: D1.1 (K), R2.1
unnamed: TP1.1, U2.25 (2CLK), U2.48 (1CLK), U17.4
unnamed: TP4.1, U4.16 (Cn+4)
unnamed: TP5.1, U5.16 (Cn+4)
unnamed: TP8.1, U8.16 (Cn+4)
unnamed: U10.6, U16.2
unnamed: U10.8, U16.1
unnamed: U7.6, U11.1
unnamed: U6.4, U11.2
unnamed: U11.4, U12.2
unnamed: U7.12, U12.1
unnamed: U13.4, U20.1
unnamed: U14.4, U15.1
unnamed: U7.8, U15.2
unnamed: U15.4, U21.1
unnamed: U16.4, U21.2
unnamed: TP2.1, U1.4, U18.25 (2CLK), U18.48 (1CLK)
unnamed: U19.4, U20.2
